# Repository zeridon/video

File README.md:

# FOSDEM Video Repository

This repository is meant to keep track of the development for video at FOSDEM.

The [hardware](https://github.com/FOSDEM/video/tree/master/hardware) subfolder contains the overview and information describing the architecture and all things hardware-related of the FOSDEM video setup.

The [software](https://github.com/FOSDEM/video/tree/master/software) subfolder contains the source of scripts and other bits and pieces.

The [instructions](https://github.com/FOSDEM/video/tree/master/instructions) subfolder contains both source files and generated PDF files with instructions and reference pictures for use during FOSDEM itself.

The [infrastructure repository](https://github.com/FOSDEM/infrastructure) contains the ansible recipes to deploy the video infrastructure.

See also https://github.com/FOSDEM/video-ms213x-status and https://github.com/FOSDEM/video-sproxy.

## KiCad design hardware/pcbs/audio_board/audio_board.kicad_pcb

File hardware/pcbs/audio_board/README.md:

# audio board

Built-in digital audio mixer board.

* Based on the Teensy 4.1 as audio DSP
* Stereo audio input and output over USB
* Four input channels
  * 3 balanced XLR inputs for line level signals
  * One stereo 3.5mm jack with mono summing
* Four output channels
  * Two balanced XLR outputs
  * Two outputs used as stereo headphones output

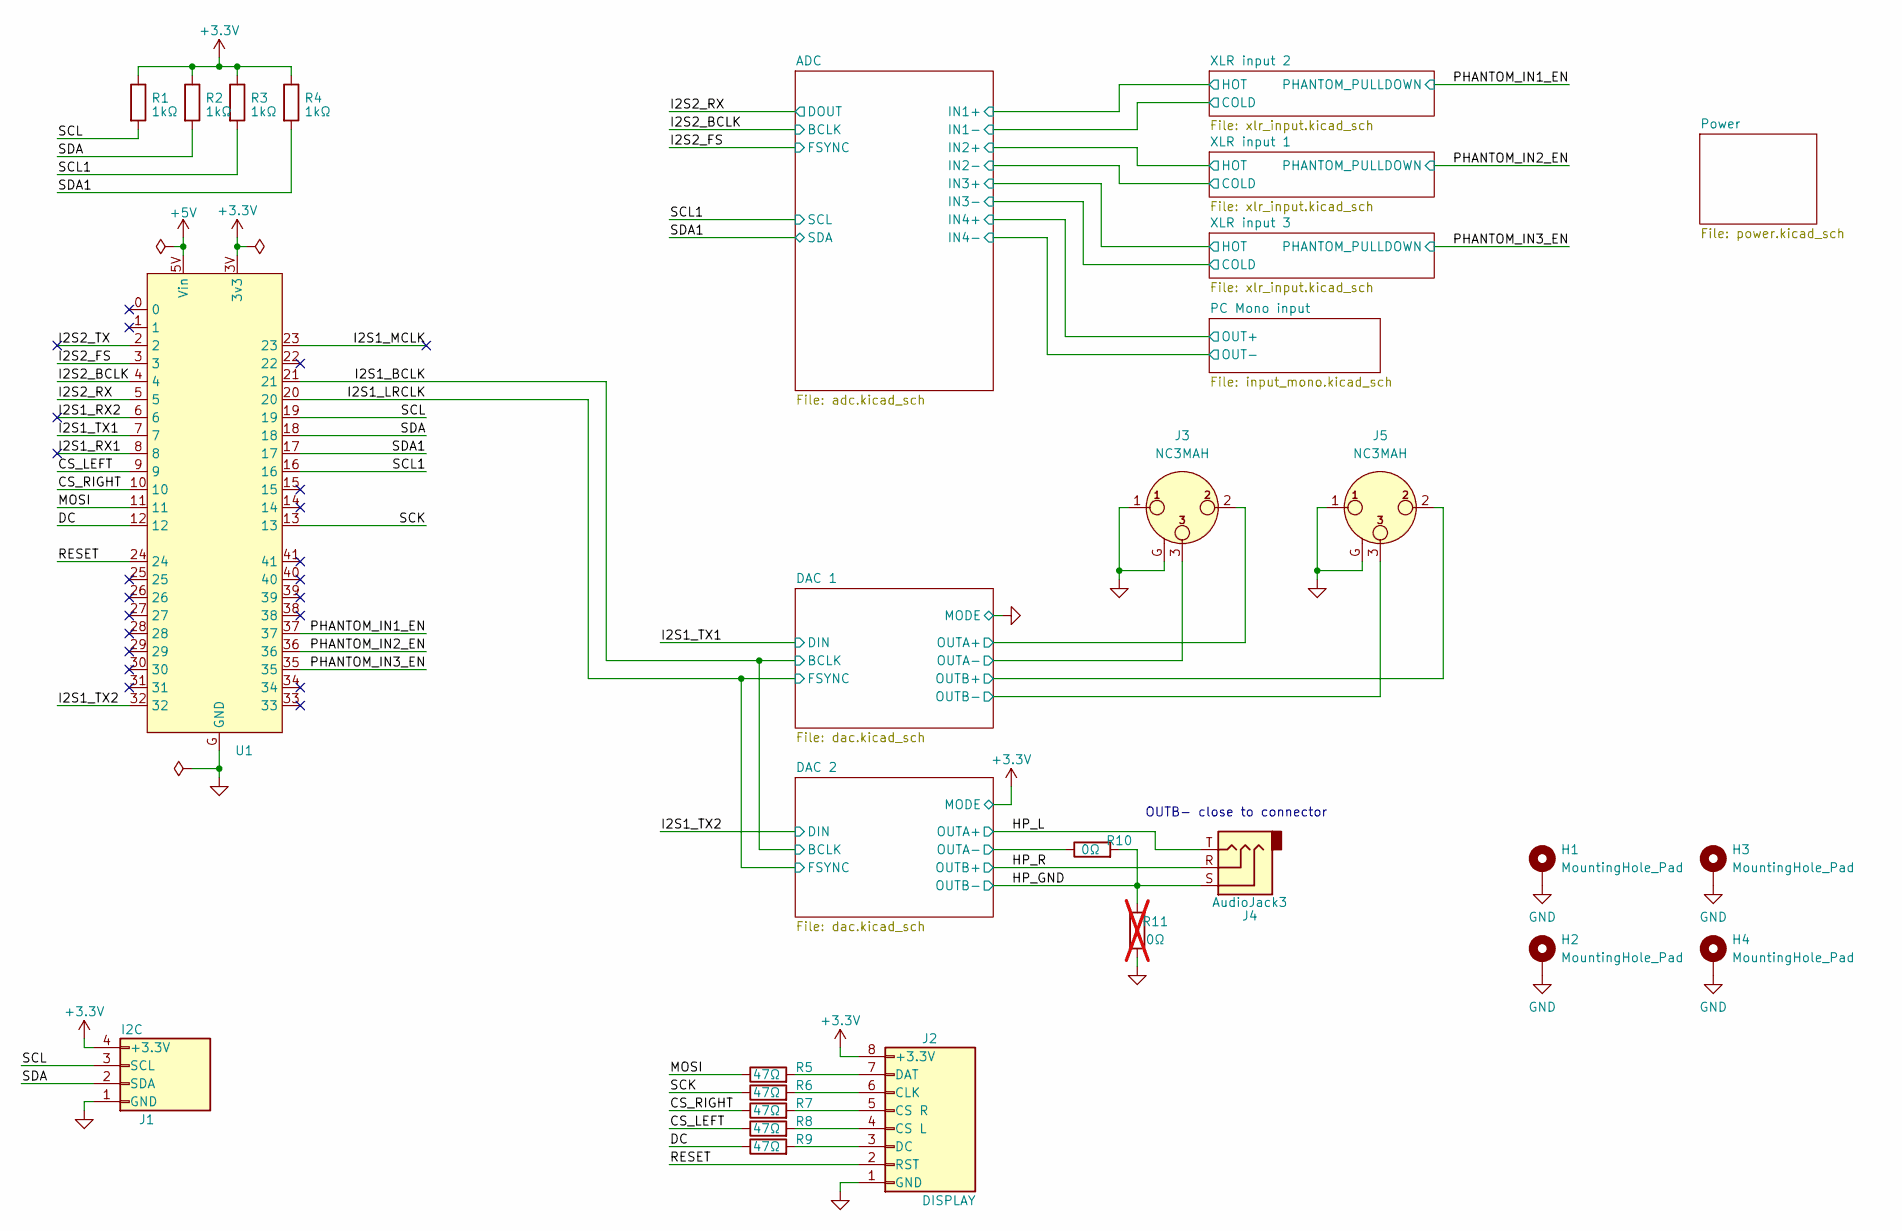
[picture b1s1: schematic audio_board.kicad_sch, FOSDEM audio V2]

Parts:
H1, H2, H3, H4: MountingHole_Pad; MountingHole_3.2mm_M3_Pad_Via
J1: Header_01x04; PinHeader_1x04_P2.54mm_Vertical; MPN PinHeader_01x04
J2: MTA100_08; mta100_01x8_P2.54_647050-8; MPN 640457-8
J3, J5: NC3MAH; Jack_XLR_Neutrik_NC3MAH_Horizontal
J4: AudioJack3; Jack_3.5mm_CUI_SJ1-3533NG_Horizontal_CircularHoles; MPN 490-SJ1-3533NG
R1, R2, R3, R4: 1kΩ; R_0805_2012Metric; MPN R 1kΩ 125mW 1% 0805
R5, R6, R7, R8, R9: 47Ω; R_0805_2012Metric; MPN R 47Ω 125mW 1% 0805
R10: 0Ω; R_0805_2012Metric; MPN R 0Ω 125mW 1% 0805
R11: 0Ω; R_0805_2012Metric; MPN R 0Ω 125mW 1% 0805; not fitted
U1: Teensy 4.1; Teensy41; MPN 2x PinSocket_1x24

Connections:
+3.3V: J1.4, J2.8, R1.1, R2.1, R3.1, R4.1, U1.3V (3v3); also elsewhere on the board
+5V: U1.5V (Vin); also elsewhere on the board
/CS_LEFT: R8.1, U1.9
/CS_RIGHT: R7.1, U1.10
/DAC 1/OUTA+: J3.2; also elsewhere on the board
/DAC 1/OUTA-: J3.3; also elsewhere on the board
/DAC 1/OUTB+: J5.2; also elsewhere on the board
/DAC 1/OUTB-: J5.3; also elsewhere on the board
/DAC 2/OUTA-: R10.1; also elsewhere on the board
/DC: R9.1, U1.12
/HP_GND: J4.S, R10.2, R11.2; also elsewhere on the board
/HP_L: J4.T; also elsewhere on the board
/HP_R: J4.R; also elsewhere on the board
/I2S1_BCLK: U1.21; also elsewhere on the board
/I2S1_LRCLK: U1.20; also elsewhere on the board
/I2S1_MCLK: U1.23
/I2S1_RX1: U1.8
/I2S1_RX2: U1.6
/I2S1_TX1: U1.7; also elsewhere on the board
/I2S1_TX2: U1.32; also elsewhere on the board
/I2S2_BCLK: U1.4; also elsewhere on the board
/I2S2_FS: U1.3; also elsewhere on the board
/I2S2_RX: U1.5; also elsewhere on the board
/I2S2_TX: U1.2
/MOSI: R5.1, U1.11
/PHANTOM_IN1_EN: U1.37; also elsewhere on the board
/PHANTOM_IN2_EN: U1.36; also elsewhere on the board
/PHANTOM_IN3_EN: U1.35; also elsewhere on the board
/RESET: J2.2, U1.24
/SCK: R6.1, U1.13
/SCL: J1.3, R1.2, U1.19
/SCL1: R3.2, U1.16; also elsewhere on the board
/SDA: J1.2, R2.2, U1.18
/SDA1: R4.2, U1.17; also elsewhere on the board
GND: H1.1, H2.1, H3.1, H4.1, J1.1, J2.1, J3.1, J3.G, J5.1, J5.G, R11.1, U1.G (GND); also elsewhere on the board
unnamed: J2.3, R9.2
unnamed: J2.4, R8.2
unnamed: J2.5, R7.2
unnamed: J2.6, R6.2
unnamed: J2.7, R5.2

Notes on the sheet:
OUTB- close to connector

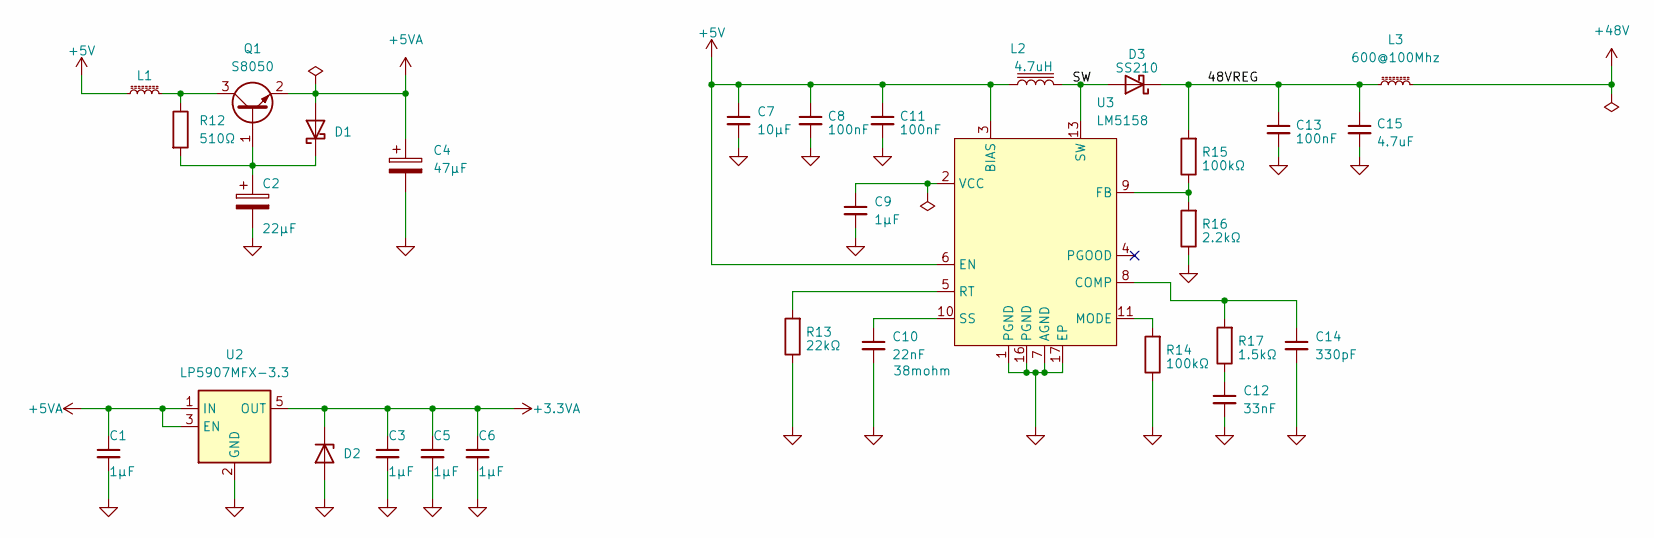
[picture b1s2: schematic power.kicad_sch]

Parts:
C1, C3, C5, C6, C9: 1μF; C_0805_2012Metric; MPN C 1μF 16V 0805
C2: 22μF; C_0805_2012Metric; MPN C 22μF 16V 0805
C4: 47μF; CP_Radial_D5.0mm_P2.00mm; MPN C 47μF 16V P2
C7: 10μF; C_0805_2012Metric; MPN C 10μF 16V 0805
C8, C11, C13: 100nF; C_0805_2012Metric; MPN C 100nF 16V 0805
C10: 22nF; C_0805_2012Metric; MPN C 22nF 16V 0805
C12: 33nF; C_0805_2012Metric; MPN C 33nF 16V 0805
C14: 330pF; C_0805_2012Metric; MPN C 330pF 16V 0805
C15: 4.7uF; C_0805_2012Metric; MPN C 4.7μF 16V 0805
D1: Schottky; D_SOD-123; MPN B0540W
D2: PTVS5V0S1UR,115; Nexperia_CFP3_SOD-123W; MPN PTVS5V0S1UR,115
D3: SS210; D_SMB; MPN SS210
L1, L3: 600@100Mhz; L_0805_2012Metric; MPN BLM21AG601SN1D
L2: 4.7uH; L_Wuerth_WE-TPC-3816; MPN 744031004
Q1: S8050; SOT-23; MPN BC817-40
R12: 510Ω; R_0805_2012Metric; MPN R 510Ω 125mW 1% 0805
R13: 22kΩ; R_0805_2012Metric; MPN R 22kΩ 125mW 1% 0805
R14, R15: 100kΩ; R_0805_2012Metric; MPN R 100kΩ 125mW 1% 0805
R16: 2.2kΩ; R_0805_2012Metric; MPN R 2.2kΩ 125mW 1% 0805
R17: 1.5kΩ; R_0805_2012Metric; MPN R 1.5kΩ 125mW 1% 0805
U2: LP5907MFX-3.3; SOT-23-5; MPN LP5907MFX-3.3
U3: LM5158; WQFN-16-1EP_3x3mm_P0.5mm_EP1.68x1.68mm_ThermalVias; MPN LM5158QRTERQ1

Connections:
+3.3VA: C3.1, C5.1, C6.1, D2.1 (K), U2.5 (OUT); also elsewhere on the board
+5V: C7.1, C8.1, C11.1, L1.1, L2.2, U3.3 (BIAS), U3.6 (EN); also elsewhere on the board
+5VA: C1.1, C4.1, D1.2 (A), Q1.2 (E), U2.1 (IN), U2.3 (EN)
+48V: L3.2; also elsewhere on the board
/Power/48VREG: C13.1, C15.1, D3.1 (K), L3.1, R15.2
/Power/SW: D3.2 (A), L2.1, U3.13 (SW), U3.14 (SW)
GND: C1.2, C2.2, C3.2, C4.2, C5.2, C6.2, C7.2, C8.2, C9.2, C10.2, C11.2, C12.2, C13.2, C14.2, C15.2, D2.2 (A), R13.1, R14.1, R16.1, U2.2 (GND), U3.1 (PGND), U3.7 (AGND), U3.16 (PGND), U3.17 (EP); also elsewhere on the board
unnamed: C12.1, R17.1
unnamed: C2.1, D1.1 (K), Q1.1 (B), R12.2
unnamed: L1.2, Q1.3 (C), R12.1
unnamed: C14.1, R17.2, U3.8 (COMP)
unnamed: R15.1, R16.2, U3.9 (FB)
unnamed: R14.2, U3.11 (MODE)
unnamed: R13.2, U3.5 (RT)
unnamed: C10.1, U3.10 (SS)
unnamed: C9.1, U3.2 (VCC)

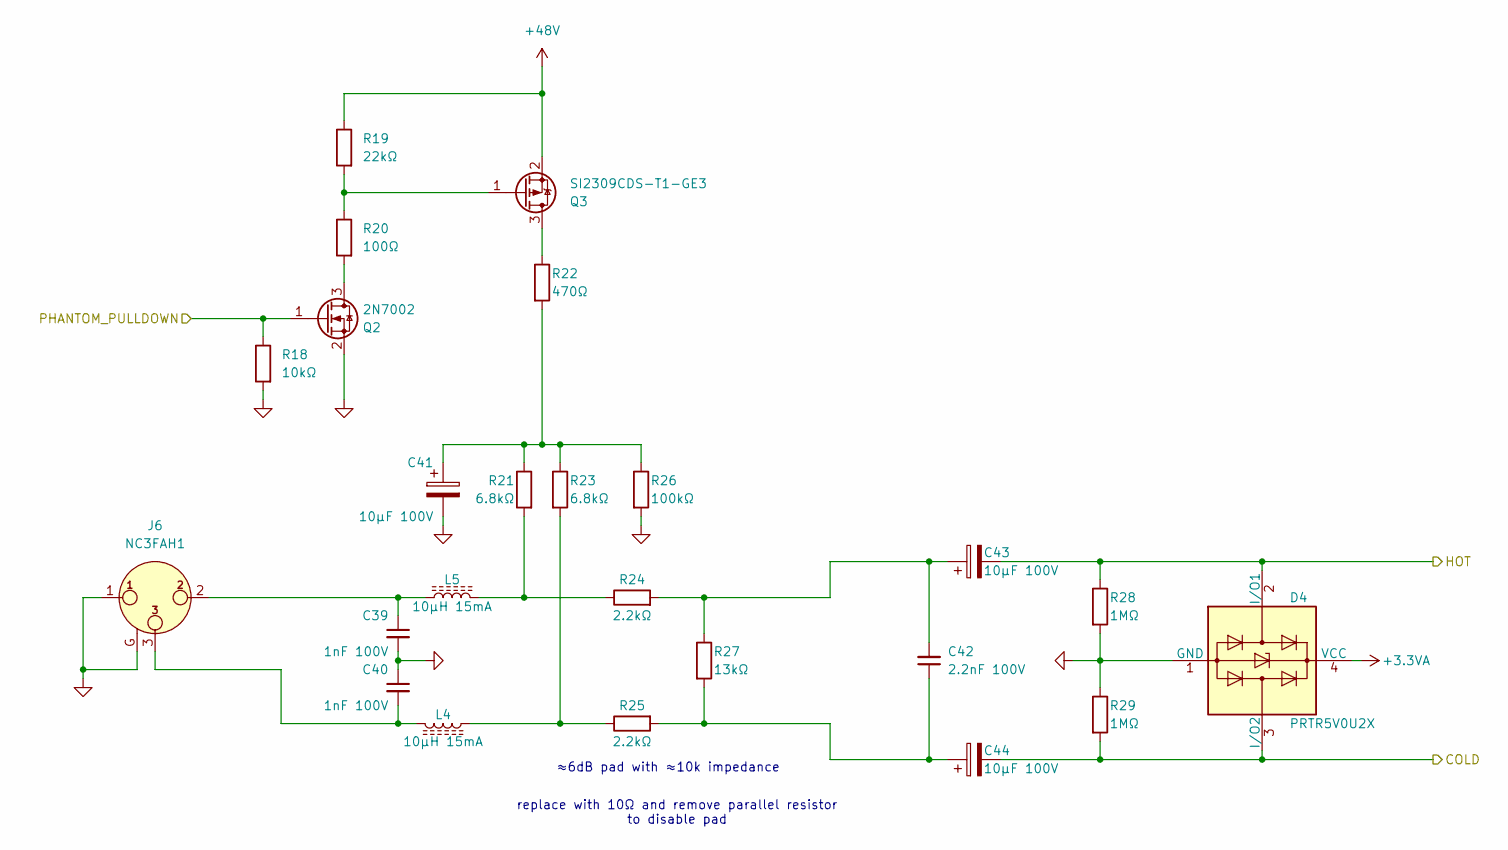
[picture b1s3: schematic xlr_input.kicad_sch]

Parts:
C39, C40: 1nF 100V; C_0805_2012Metric; MPN C 1nF LowESR 100V 0805
C41: 10μF 100V; CP_Radial_D5.0mm_P2.00mm; MPN C 10μF 100V P2
C42: 2.2nF 100V; C_0805_2012Metric; MPN C 2.2nF LowESR 100V 0805
C43, C44: 10μF 100V; CP_Radial_D5.0mm_P2.00mm; MPN C 10μF LowESR 100V P2
D4: PRTR5V0U2X; SOT-143; MPN PRTR5V0U2X,215
J6: NC3FAH1; Jack_XLR_Neutrik_NC3FAH2-LR-DAE_Horizontal; MPN NC3FAH1
L4, L5: 10μH 15mA; L_0805_2012Metric; MPN LQM21FN100N00L
Q2: 2N7002; SOT-23; MPN 2N7002
Q3: SI2309CDS-T1-GE3; SOT-23; MPN SI2309CDS-T1-GE3
R18: 10kΩ; R_0805_2012Metric; MPN R 10kΩ 125mW 1% 0805
R19: 22kΩ; R_0805_2012Metric; MPN R 22kΩ 125mW 1% 0805
R20: 100Ω; R_0805_2012Metric; MPN R 100Ω 125mW 1% 0805
R21, R23: 6.8kΩ; R_0805_2012Metric; MPN R 6.8kΩ 125mW 1% 0805
R22: 470Ω; R_0805_2012Metric; MPN R 470Ω 125mW 1% 0805
R24, R25: 2.2kΩ; R_0805_2012Metric; MPN R 2.2kΩ 125mW 1% 0805
R26: 100kΩ; R_0805_2012Metric; MPN R 100kΩ 125mW 1% 0805
R27: 13kΩ; R_0805_2012Metric; MPN R 13kΩ 125mW 1% 0805
R28, R29: 1MΩ; R_0805_2012Metric; MPN R 1MΩ 125mW 1% 0805

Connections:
+3.3VA: D4.4 (VCC); also elsewhere on the board
+48V: Q3.2 (S), R19.1; also elsewhere on the board
/ADC/IN2+: C43.2, D4.2 (I/O1), R28.1; also elsewhere on the board
/ADC/IN2-: C44.2, D4.3 (I/O2), R29.2; also elsewhere on the board
/PHANTOM_IN2_EN: Q2.1 (G), R18.1; also elsewhere on the board
GND: C39.2, C40.1, C41.2, D4.1 (GND), J6.1, J6.G, Q2.2 (S), R18.2, R26.2, R28.2, R29.1; also elsewhere on the board
unnamed: C39.1, J6.2, L5.1
unnamed: C40.2, J6.3, L4.1
unnamed: C41.1, R21.1, R22.2, R23.1, R26.1
unnamed: C42.1, C44.1, R25.2, R27.2
unnamed: C42.2, C43.1, R24.2, R27.1
unnamed: L4.2, R23.2, R25.1
unnamed: L5.2, R21.2, R24.1
unnamed: Q2.3 (D), R20.2
unnamed: Q3.3 (D), R22.1
unnamed: Q3.1 (G), R19.2, R20.1

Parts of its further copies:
C45, C46, C51, C52: 1nF 100V; C_0805_2012Metric; MPN C 1nF LowESR 100V 0805
C47, C53: 10μF 100V; CP_Radial_D5.0mm_P2.00mm; MPN C 10μF 100V P2
C48, C54: 2.2nF 100V; C_0805_2012Metric; MPN C 2.2nF LowESR 100V 0805
C49, C50, C55, C56: 10μF 100V; CP_Radial_D5.0mm_P2.00mm; MPN C 10μF LowESR 100V P2
D5, D6: PRTR5V0U2X; SOT-143; MPN PRTR5V0U2X,215
J7, J8: NC3FAH1; Jack_XLR_Neutrik_NC3FAH2-LR-DAE_Horizontal; MPN NC3FAH1
L6, L7, L8, L9: 10μH 15mA; L_0805_2012Metric; MPN LQM21FN100N00L
Q4, Q6: 2N7002; SOT-23; MPN 2N7002
Q5, Q7: SI2309CDS-T1-GE3; SOT-23; MPN SI2309CDS-T1-GE3
R30, R42: 10kΩ; R_0805_2012Metric; MPN R 10kΩ 125mW 1% 0805
R31, R43: 22kΩ; R_0805_2012Metric; MPN R 22kΩ 125mW 1% 0805
R32, R44: 100Ω; R_0805_2012Metric; MPN R 100Ω 125mW 1% 0805
R33, R35, R45, R47: 6.8kΩ; R_0805_2012Metric; MPN R 6.8kΩ 125mW 1% 0805
R34, R46: 470Ω; R_0805_2012Metric; MPN R 470Ω 125mW 1% 0805
R36, R37, R48, R49: 2.2kΩ; R_0805_2012Metric; MPN R 2.2kΩ 125mW 1% 0805
R38, R50: 100kΩ; R_0805_2012Metric; MPN R 100kΩ 125mW 1% 0805
R39, R51: 13kΩ; R_0805_2012Metric; MPN R 13kΩ 125mW 1% 0805
R40, R41, R52, R53: 1MΩ; R_0805_2012Metric; MPN R 1MΩ 125mW 1% 0805

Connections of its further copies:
+3.3VA: D5.4 (VCC), D6.4 (VCC); also elsewhere on the board
+48V: Q5.2 (S), Q7.2 (S), R31.1, R43.1; also elsewhere on the board
/ADC/IN1+: C49.2, D5.2 (I/O1), R40.1; also elsewhere on the board
/ADC/IN1-: C50.2, D5.3 (I/O2), R41.2; also elsewhere on the board
/ADC/IN3+: C55.2, D6.2 (I/O1), R52.1; also elsewhere on the board
/ADC/IN3-: C56.2, D6.3 (I/O2), R53.2; also elsewhere on the board
/PHANTOM_IN1_EN: Q4.1 (G), R30.1; also elsewhere on the board
/PHANTOM_IN3_EN: Q6.1 (G), R42.1; also elsewhere on the board
GND: C45.2, C46.1, C47.2, C51.2, C52.1, C53.2, D5.1 (GND), D6.1 (GND), J7.1, J7.G, J8.1, J8.G, Q4.2 (S), Q6.2 (S), R30.2, R38.2, R40.2, R41.1, R42.2, R50.2, R52.2, R53.1; also elsewhere on the board
unnamed: C45.1, J7.2, L7.1
unnamed: C46.2, J7.3, L6.1
unnamed: C47.1, R33.1, R34.2, R35.1, R38.1
unnamed: C48.1, C50.1, R37.2, R39.2
unnamed: C48.2, C49.1, R36.2, R39.1
unnamed: C51.1, J8.2, L9.1
unnamed: C52.2, J8.3, L8.1
unnamed: C53.1, R45.1, R46.2, R47.1, R50.1
unnamed: C54.1, C56.1, R49.2, R51.2
unnamed: C54.2, C55.1, R48.2, R51.1
unnamed: L6.2, R35.2, R37.1
unnamed: L7.2, R33.2, R36.1
unnamed: L8.2, R47.2, R49.1
unnamed: L9.2, R45.2, R48.1
unnamed: Q4.3 (D), R32.2
unnamed: Q5.3 (D), R34.1
unnamed: Q5.1 (G), R31.2, R32.1
unnamed: Q6.3 (D), R44.2
unnamed: Q7.3 (D), R46.1
unnamed: Q7.1 (G), R43.2, R44.1

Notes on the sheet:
replace with 10Ω and remove parallel resistor to disable pad
≈6dB pad with ≈10k impedance

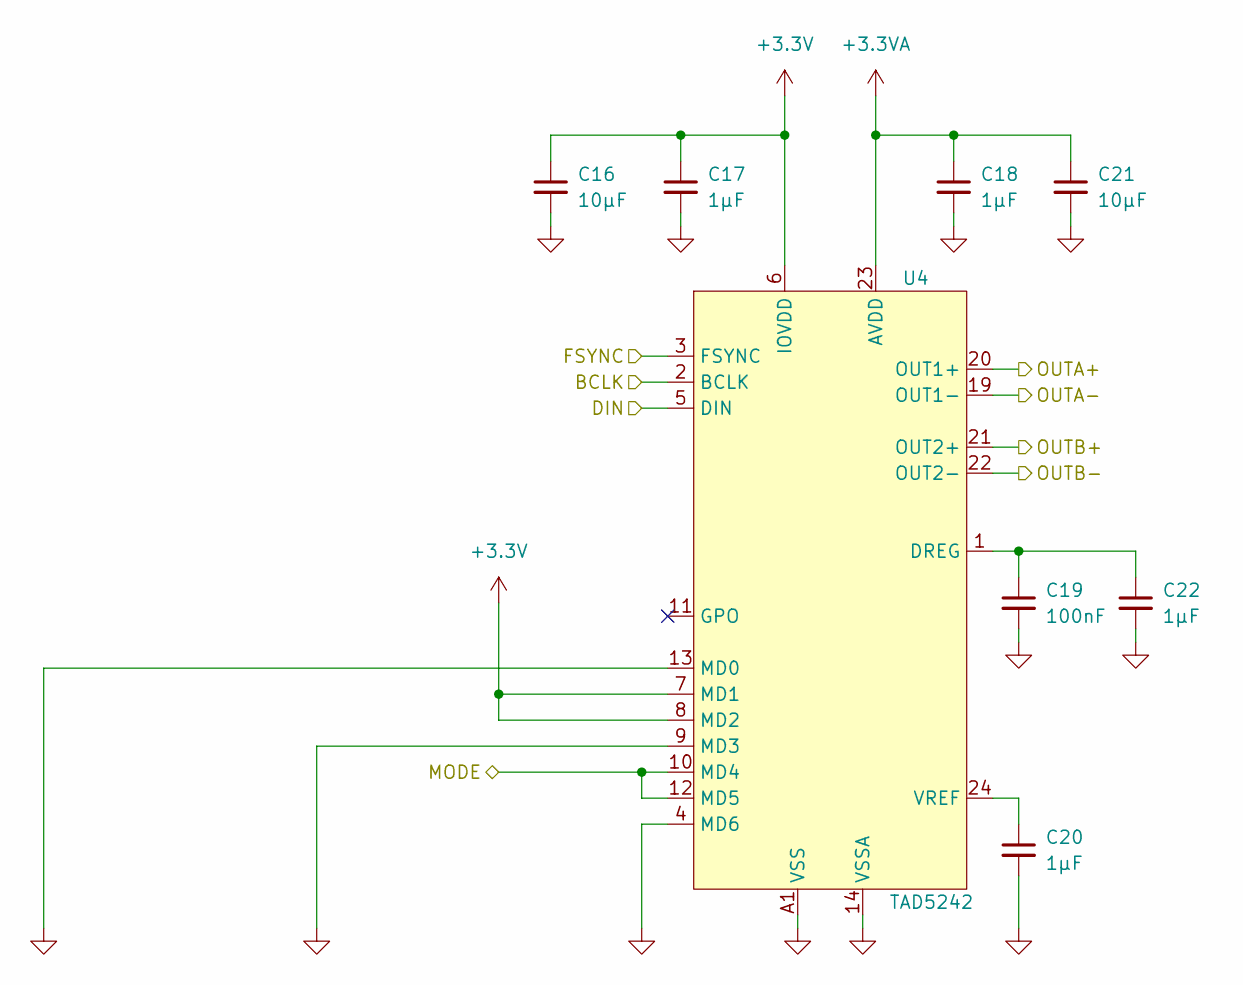
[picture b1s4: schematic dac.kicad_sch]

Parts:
C16, C21: 10μF; C_0805_2012Metric; MPN C 10μF 16V 0805
C17, C18, C20, C22: 1μF; C_0805_2012Metric; MPN C 1μF 16V 0805
C19: 100nF; C_0805_2012Metric; MPN C 100nF 16V 0805
U4: TAD5242; Texas_RGE0024R_VQFN-24-1EP_4x4mm_P0.5mm_EP2.1x2.1mm; MPN TAD5242IRGER

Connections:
+3.3V: C16.1, C17.1, U4.6 (IOVDD), U4.7 (MD1), U4.8 (MD2); also elsewhere on the board
+3.3VA: C18.1, C21.1, U4.23 (AVDD); also elsewhere on the board
/DAC 1/OUTA+: U4.20 (OUT1+); also elsewhere on the board
/DAC 1/OUTA-: U4.19 (OUT1-); also elsewhere on the board
/DAC 1/OUTB+: U4.21 (OUT2+); also elsewhere on the board
/DAC 1/OUTB-: U4.22 (OUT2-); also elsewhere on the board
/I2S1_BCLK: U4.2 (BCLK); also elsewhere on the board
/I2S1_LRCLK: U4.3 (FSYNC); also elsewhere on the board
/I2S1_TX1: U4.5 (DIN); also elsewhere on the board
GND: C16.2, C17.2, C18.2, C19.2, C20.2, C21.2, C22.2, U4.4 (MD6), U4.9 (MD3), U4.10 (MD4), U4.12 (MD5), U4.13 (MD0), U4.14 (VSSA), U4.15 (VSSA), U4.16 (VSSA), U4.17 (VSSA), U4.18 (VSSA), U4.25 (VSS), U4.A1 (VSS), U4.A2 (VSS), U4.A3 (VSS), U4.A4 (VSS); also elsewhere on the board
unnamed: C19.1, C22.1, U4.1 (DREG)
unnamed: C20.1, U4.24 (VREF)

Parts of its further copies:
C23, C28: 10μF; C_0805_2012Metric; MPN C 10μF 16V 0805
C24, C25, C27, C29: 1μF; C_0805_2012Metric; MPN C 1μF 16V 0805
C26: 100nF; C_0805_2012Metric; MPN C 100nF 16V 0805
U5: TAD5242; Texas_RGE0024R_VQFN-24-1EP_4x4mm_P0.5mm_EP2.1x2.1mm; MPN TAD5242IRGER

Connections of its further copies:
+3.3V: C23.1, C24.1, U5.6 (IOVDD), U5.7 (MD1), U5.8 (MD2), U5.10 (MD4), U5.12 (MD5); also elsewhere on the board
+3.3VA: C25.1, C28.1, U5.23 (AVDD); also elsewhere on the board
/DAC 2/OUTA-: U5.19 (OUT1-); also elsewhere on the board
/HP_GND: U5.22 (OUT2-); also elsewhere on the board
/HP_L: U5.20 (OUT1+); also elsewhere on the board
/HP_R: U5.21 (OUT2+); also elsewhere on the board
/I2S1_BCLK: U5.2 (BCLK); also elsewhere on the board
/I2S1_LRCLK: U5.3 (FSYNC); also elsewhere on the board
/I2S1_TX2: U5.5 (DIN); also elsewhere on the board
GND: C23.2, C24.2, C25.2, C26.2, C27.2, C28.2, C29.2, U5.4 (MD6), U5.9 (MD3), U5.13 (MD0), U5.14 (VSSA), U5.15 (VSSA), U5.16 (VSSA), U5.17 (VSSA), U5.18 (VSSA), U5.25 (VSS), U5.A1 (VSS), U5.A2 (VSS), U5.A3 (VSS), U5.A4 (VSS); also elsewhere on the board
unnamed: C26.1, C29.1, U5.1 (DREG)
unnamed: C27.1, U5.24 (VREF)

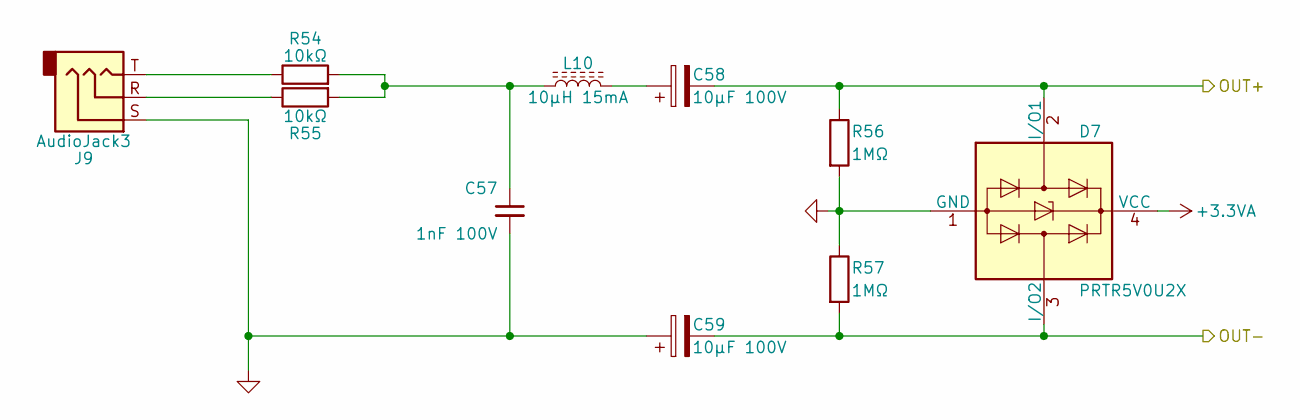
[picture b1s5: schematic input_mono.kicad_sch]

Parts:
C57: 1nF 100V; C_0805_2012Metric; MPN C 1nF LowESR 100V 0805
C58, C59: 10μF 100V; CP_Radial_D5.0mm_P2.00mm; MPN C 10μF LowESR 100V P2
D7: PRTR5V0U2X; SOT-143; MPN PRTR5V0U2X,215
J9: AudioJack3; Jack_3.5mm_CUI_SJ1-3533NG_Horizontal_CircularHoles; MPN 490-SJ1-3533NG
L10: 10μH 15mA; L_0805_2012Metric; MPN LQM21FN100N00L
R54, R55: 10kΩ; R_0805_2012Metric; MPN R 10kΩ 125mW 1% 0805
R56, R57: 1MΩ; R_0805_2012Metric; MPN R 1MΩ 125mW 1% 0805

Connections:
+3.3VA: D7.4 (VCC); also elsewhere on the board
/ADC/IN4+: C58.2, D7.2 (I/O1), R56.1; also elsewhere on the board
/ADC/IN4-: C59.2, D7.3 (I/O2), R57.2; also elsewhere on the board
GND: C57.2, C59.1, D7.1 (GND), J9.S, R56.2, R57.1; also elsewhere on the board
unnamed: C57.1, L10.1, R54.2, R55.2
unnamed: C58.1, L10.2
unnamed: J9.R, R55.1
unnamed: J9.T, R54.1

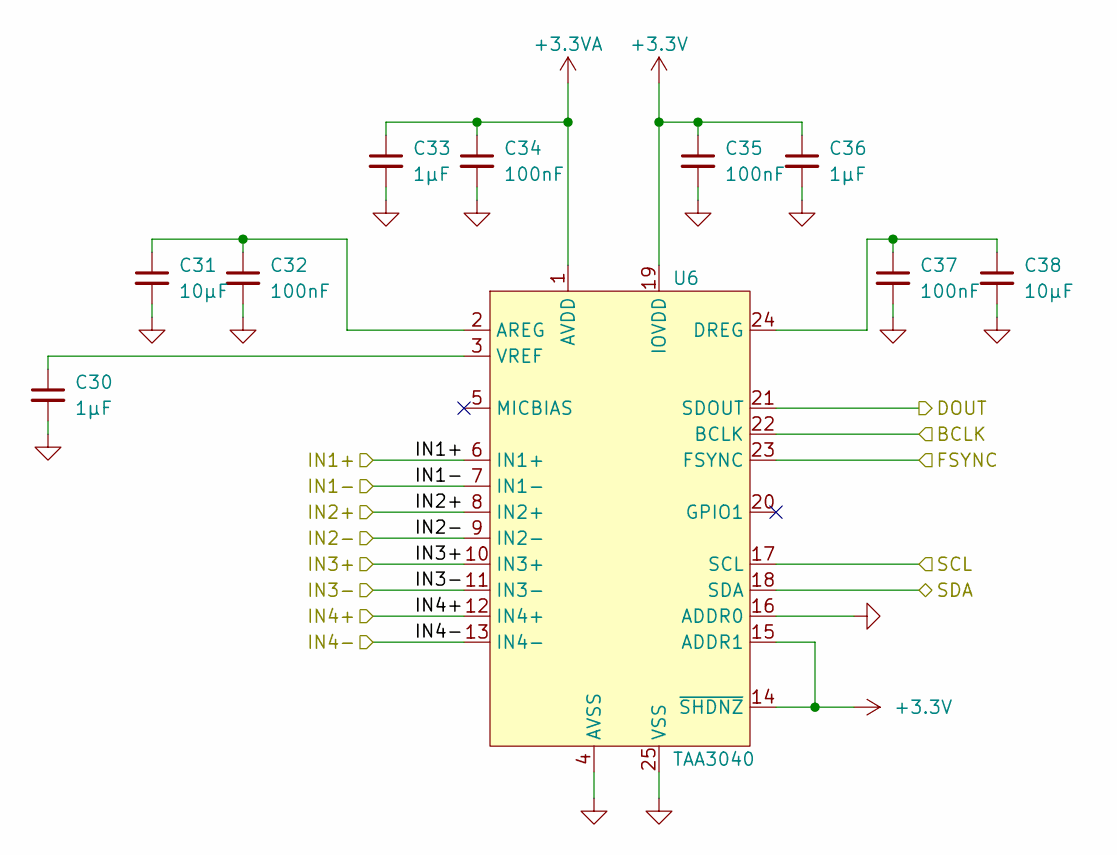
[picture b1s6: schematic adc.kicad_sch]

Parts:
C30, C33, C36: 1μF; C_0805_2012Metric; MPN C 1μF 16V 0805
C31, C38: 10μF; C_0805_2012Metric; MPN C 10μF 16V 0805
C32, C34, C35, C37: 100nF; C_0805_2012Metric; MPN C 100nF 16V 0805
U6: TAA3040; WQFN-24-1EP_4x4mm_P0.5mm_EP2.6x2.6mm; MPN TAA3040IRTWR

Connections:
+3.3V: C35.1, C36.1, U6.14 (~SHDNZ), U6.15 (ADDR1), U6.19 (IOVDD); also elsewhere on the board
+3.3VA: C33.1, C34.1, U6.1 (AVDD); also elsewhere on the board
/ADC/IN1+: U6.6 (IN1+); also elsewhere on the board
/ADC/IN1-: U6.7 (IN1-); also elsewhere on the board
/ADC/IN2+: U6.8 (IN2+); also elsewhere on the board
/ADC/IN2-: U6.9 (IN2-); also elsewhere on the board
/ADC/IN3+: U6.10 (IN3+); also elsewhere on the board
/ADC/IN3-: U6.11 (IN3-); also elsewhere on the board
/ADC/IN4+: U6.12 (IN4+); also elsewhere on the board
/ADC/IN4-: U6.13 (IN4-); also elsewhere on the board
/I2S2_BCLK: U6.22 (BCLK); also elsewhere on the board
/I2S2_FS: U6.23 (FSYNC); also elsewhere on the board
/I2S2_RX: U6.21 (SDOUT); also elsewhere on the board
/SCL1: U6.17 (SCL); also elsewhere on the board
/SDA1: U6.18 (SDA); also elsewhere on the board
GND: C30.2, C31.2, C32.2, C33.2, C34.2, C35.2, C36.2, C37.2, C38.2, U6.4 (AVSS), U6.16 (ADDR0), U6.25 (VSS); also elsewhere on the board
unnamed: C31.1, C32.1, U6.2 (AREG)
unnamed: C37.1, C38.1, U6.24 (DREG)
unnamed: C30.1, U6.3 (VREF)

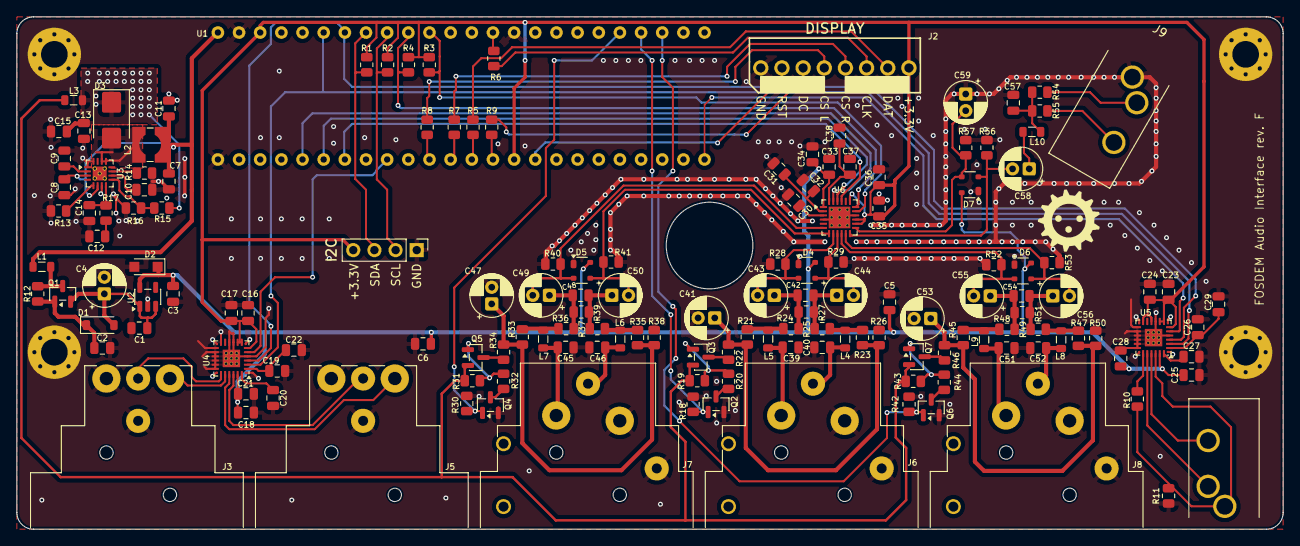
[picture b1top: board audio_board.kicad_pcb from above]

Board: 4 copper layers, 152.0 x 61.5 mm, 159 parts (0 on the bottom side), 99 nets.

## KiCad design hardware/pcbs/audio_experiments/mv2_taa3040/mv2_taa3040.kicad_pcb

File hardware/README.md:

# Parts

A full build needs several parts. All of these should be easily reproducible,
while for the ones where we rely on an external manufacturer, we made sure to
have ample spares.

You will need one of each item, except when stated otherwise.

## Case

The case is an off-the-shelf widely available 1U case, made by Gainta.

  * [G17081UBK](https://www.gainta.com/en/g17081ubk.html)

We only use the actual enclosure. All other bits can be discarded.

Each side of the case has 8 4mm high screw holes. These are just too tight to
fit our standard M3 bolts, so we will need to enlarge them. Using a manual
threading tool works, but using a drill press with a 2.8mm drill works best.

## Front

The front is made out of 2.5mm MDF and cut using a laser cutter, see `frontplate/`

## Back

The back is made out of 2.5mm MDF and cut using a laser cutter, see `backplate/`

## Boards

### Externally sourced

The boards are the hardest part to source, so we made sure to have ample stock
to last us a while.

  * [MS2131 board](https://www.shophagibis.com/products/video-capture-card-hagibis?variant=45797324783897)
  * [Raxda X4](https://radxa.com/products/x/x4/)

The MS2131 board we started off with is the demo board as produced by Ultrasemi.
Currently we use the Hagibis version, as this proved to be the most stable from
all MS2131 boards we tested.

The Raxda X4 is a x86-based SBC that handles all computing needs.

### Boards we make

* Ethernet switch
* Power board
* Audio mixer

## Cables

* 6 x MTA100 cables (white ones) to connect "hats"
* 2 x USB 3.0 A-A cables, any cable should do. We used a "Vention CONBD".
* 1 x USB 2.0 A-microUSB to connect the Teensy on the audio mixed
* 1 x HDMI-to-microHDMI cable for the loop-out from radxa
* 1 x ethernet cable from Radxa to the switch
* 1 x power cable from the power board to the Radxa
* 1 x power cable from the external jack to the power board

## Connectors

We expose:

* HDMI IN, HDMI loop out from the MS2131;
* HDMI out from the Radxa via a Neutrik connector
* 4 x ethernet ports
* 3 x audio inputs, XLR
* 2 x audio outputs, XLR
* 1 x headphone jack

## Bits and bobs

TBD 

# Production

See `assembly`.

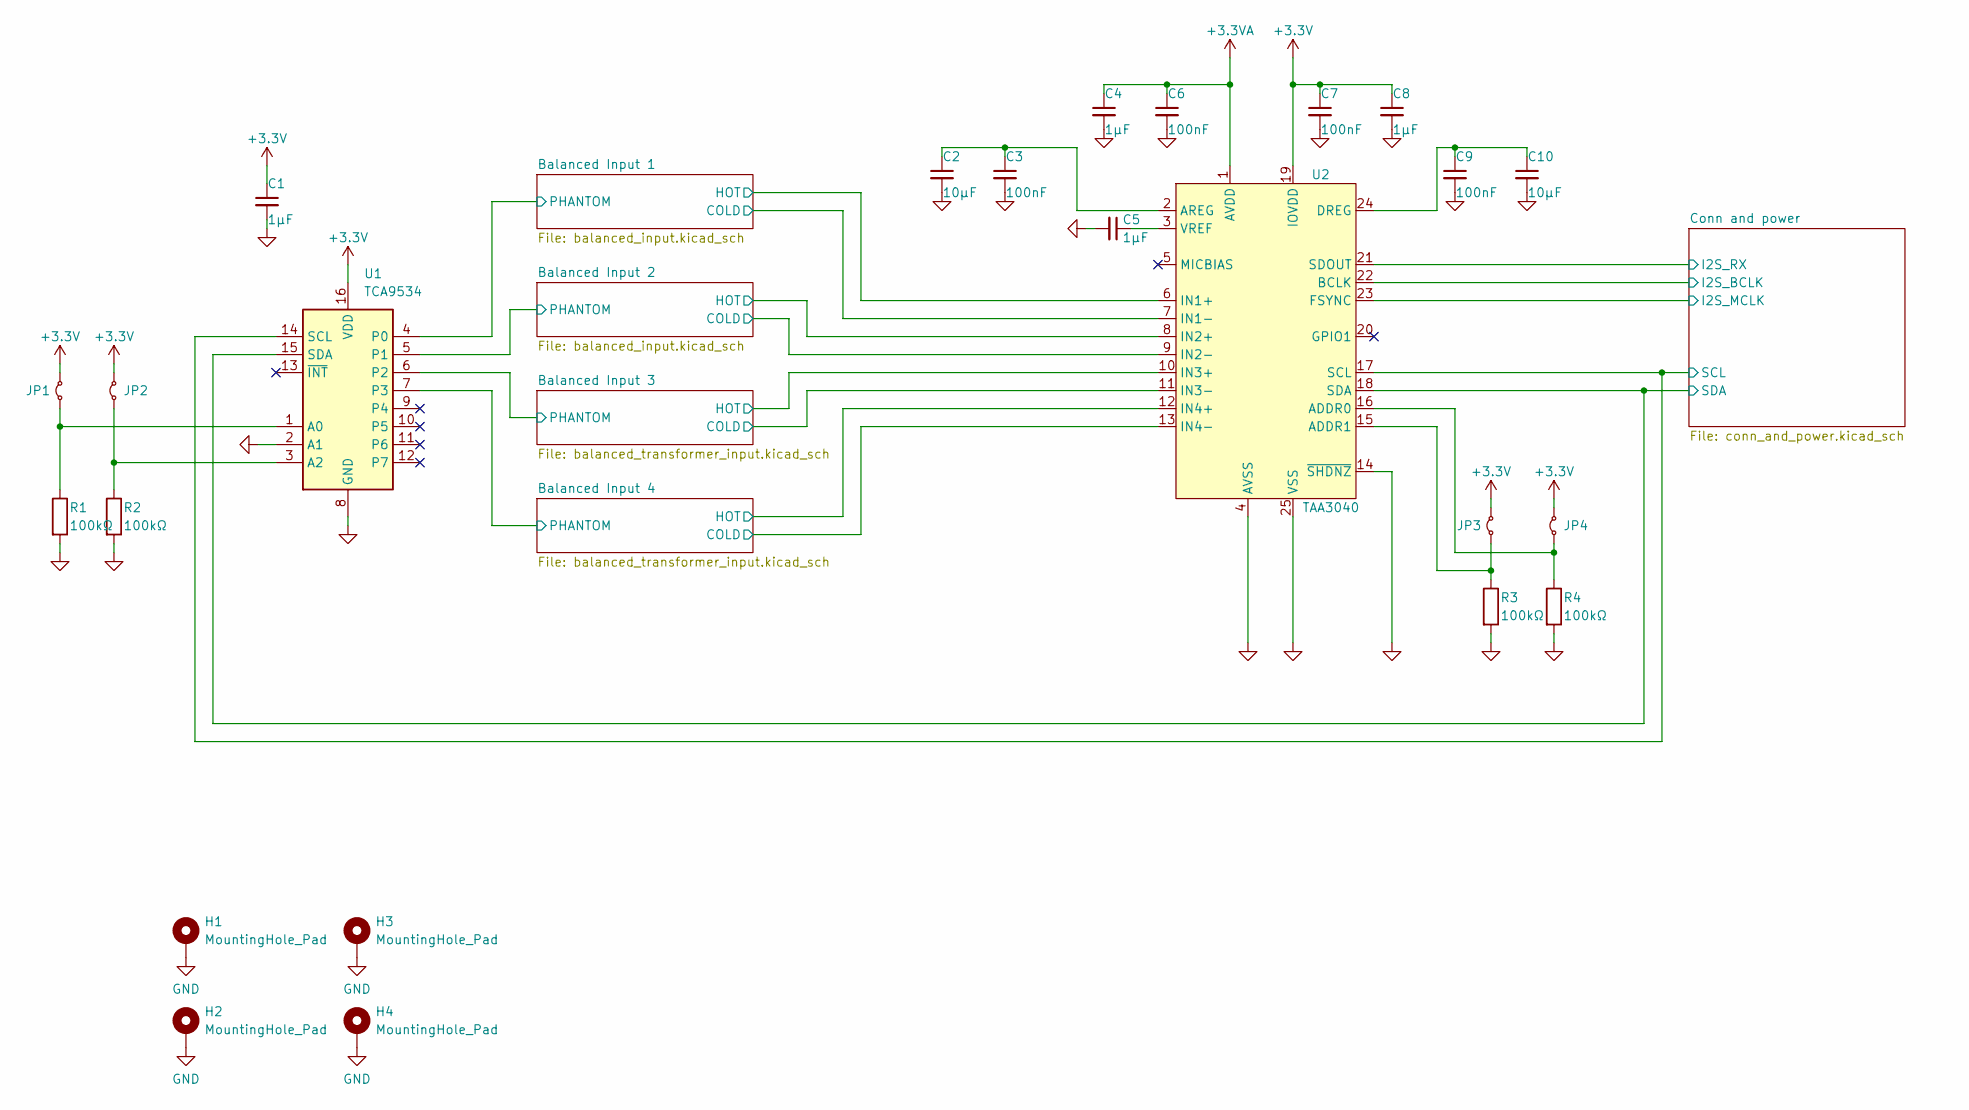
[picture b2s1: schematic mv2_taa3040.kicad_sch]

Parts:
C1, C4, C5, C8: 1μF; C_0805_2012Metric; MPN C 1μF 16V 0805
C2, C10: 10μF; C_0805_2012Metric; MPN C 10μF 16V 0805
C3, C6, C7, C9: 100nF; C_0603_1608Metric; MPN C 100nF 16V 0603
H1, H2, H3, H4: MountingHole_Pad; MountingHole_3.2mm_M3_Pad_Via
JP1, JP2, JP3, JP4: Jumper_2_Small_Bridged; SolderJumper-2_P1.3mm_Open_RoundedPad1.0x1.5mm
R1, R2, R3, R4: 100kΩ; R_0603_1608Metric; MPN R 100kΩ 125mW 5% 0603
U1: TCA9534; SOIC-16W_7.5x10.3mm_P1.27mm; Part TCA9534DWR; LCSC C2870609
U2: TAA3040; WQFN-24-1EP_4x4mm_P0.5mm_EP2.6x2.6mm; MPN TAA3040IRTWR

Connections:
+3.3V: C1.1, C7.1, C8.1, JP1.2 (B), JP2.2 (B), JP3.2 (B), JP4.2 (B), U1.16 (VDD), U2.19 (IOVDD); also elsewhere on the board
+3.3VA: C4.1, C6.1, U2.1 (AVDD); also elsewhere on the board
/Balanced Input 1/COLD: U2.7 (IN1-); also elsewhere on the board
/Balanced Input 1/HOT: U2.6 (IN1+); also elsewhere on the board
/Balanced Input 1/PHANTOM: U1.4 (P0); also elsewhere on the board
/Balanced Input 2/COLD: U2.9 (IN2-); also elsewhere on the board
/Balanced Input 2/HOT: U2.8 (IN2+); also elsewhere on the board
/Balanced Input 2/PHANTOM: U1.5 (P1); also elsewhere on the board
/Balanced Input 3/COLD: U2.11 (IN3-); also elsewhere on the board
/Balanced Input 3/HOT: U2.10 (IN3+); also elsewhere on the board
/Balanced Input 3/PHANTOM: U1.6 (P2); also elsewhere on the board
/Balanced Input 4/COLD: U2.13 (IN4-); also elsewhere on the board
/Balanced Input 4/HOT: U2.12 (IN4+); also elsewhere on the board
/Balanced Input 4/PHANTOM: U1.7 (P3); also elsewhere on the board
/Conn and power/I2S_BCLK: U2.22 (BCLK); also elsewhere on the board
/Conn and power/I2S_MCLK: U2.23 (FSYNC); also elsewhere on the board
/Conn and power/I2S_RX: U2.21 (SDOUT); also elsewhere on the board
/Conn and power/SCL: U1.14 (SCL), U2.17 (SCL); also elsewhere on the board
/Conn and power/SDA: U1.15 (SDA), U2.18 (SDA); also elsewhere on the board
GND: C1.2, C2.2, C3.2, C4.2, C5.2, C6.2, C7.2, C8.2, C9.2, C10.2, H1.1, H2.1, H3.1, H4.1, R1.2, R2.2, R3.2, R4.2, U1.2 (A1), U1.8 (GND), U2.4 (AVSS), U2.14 (~SHDNZ), U2.25 (VSS); also elsewhere on the board
unnamed: JP1.1 (A), R1.1, U1.1 (A0)
unnamed: JP2.1 (A), R2.1, U1.3 (A2)
unnamed: JP3.1 (A), R3.1, U2.15 (ADDR1)
unnamed: JP4.1 (A), R4.1, U2.16 (ADDR0)
unnamed: C2.1, C3.1, U2.2 (AREG)
unnamed: C9.1, C10.1, U2.24 (DREG)
unnamed: C5.1, U2.3 (VREF)

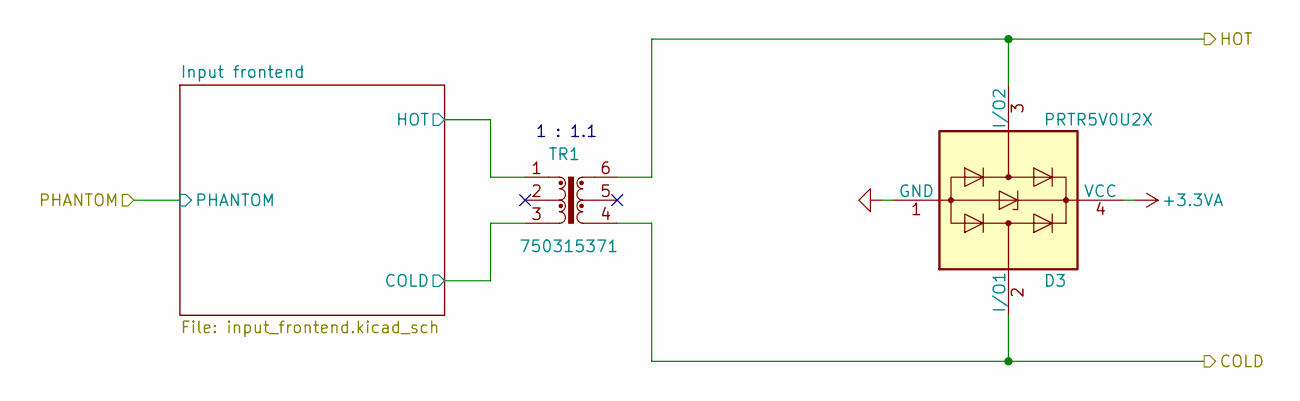
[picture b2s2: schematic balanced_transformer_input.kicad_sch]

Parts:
D3: PRTR5V0U2X; SOT-143; MPN PRTR5V0U2X,215; LCSC C12333
TR1: 750315371; Transformer_Wuerth_750315371; MPN 750315371

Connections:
+3.3VA: D3.4 (VCC); also elsewhere on the board
/Balanced Input 4/COLD: D3.2 (I/O1), TR1.4; also elsewhere on the board
/Balanced Input 4/HOT: D3.3 (I/O2), TR1.6; also elsewhere on the board
/Balanced Input 4/Input frontend/COLD: TR1.3; also elsewhere on the board
/Balanced Input 4/Input frontend/HOT: TR1.1; also elsewhere on the board
GND: D3.1 (GND); also elsewhere on the board

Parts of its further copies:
D4: PRTR5V0U2X; SOT-143; MPN PRTR5V0U2X,215; LCSC C12333
TR2: 750315371; Transformer_Wuerth_750315371; MPN 750315371

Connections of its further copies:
+3.3VA: D4.4 (VCC); also elsewhere on the board
/Balanced Input 3/COLD: D4.2 (I/O1), TR2.4; also elsewhere on the board
/Balanced Input 3/HOT: D4.3 (I/O2), TR2.6; also elsewhere on the board
/Balanced Input 3/Input frontend/COLD: TR2.3; also elsewhere on the board
/Balanced Input 3/Input frontend/HOT: TR2.1; also elsewhere on the board
GND: D4.1 (GND); also elsewhere on the board

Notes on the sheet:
1 : 1.1
